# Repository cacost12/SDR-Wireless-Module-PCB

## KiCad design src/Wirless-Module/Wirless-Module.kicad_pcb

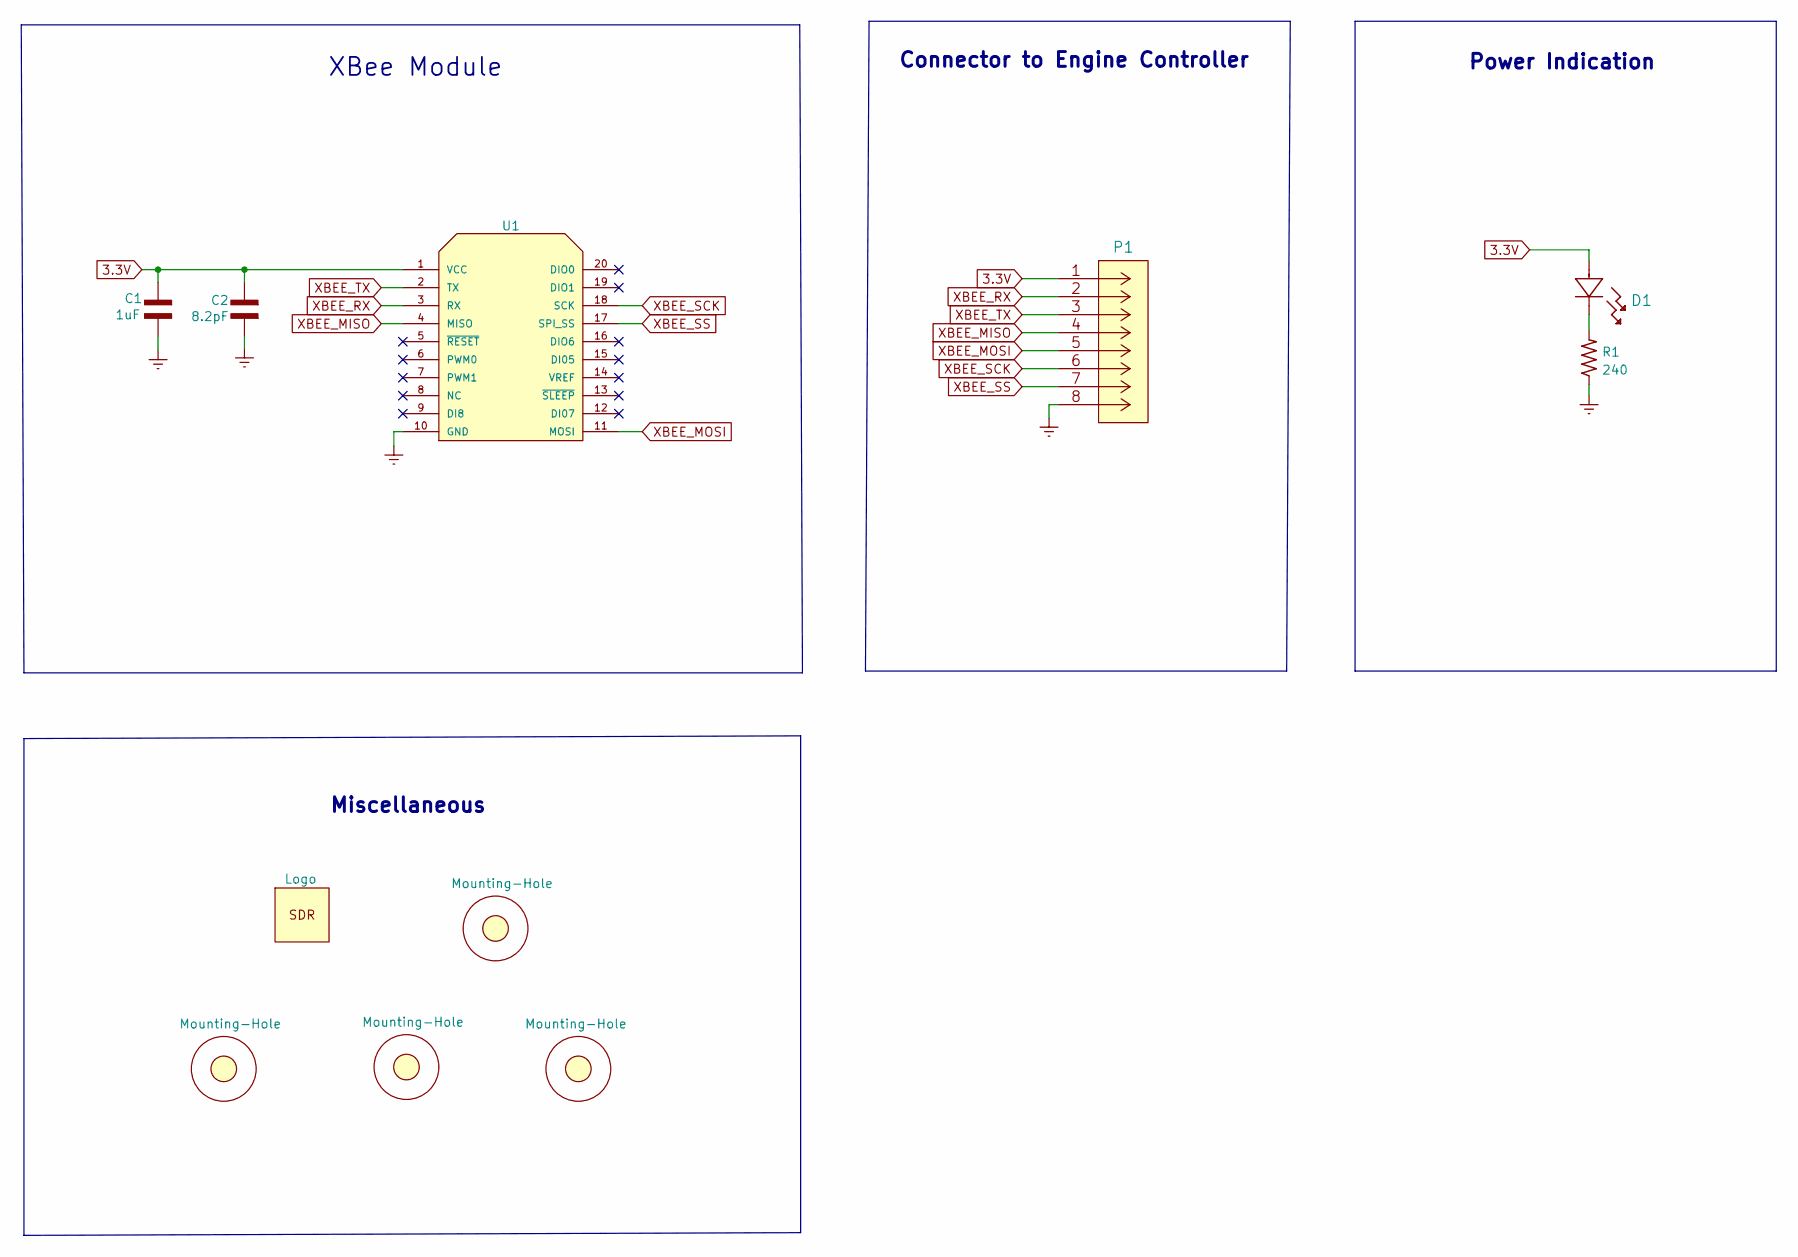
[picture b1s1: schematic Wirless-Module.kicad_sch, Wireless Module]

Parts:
C1: 1uF; CAP_0603
C2: 8.2pF; CAP_0603
D1: SML-LX1206GC-TR
H1, H2, H3, H4: Mounting-Hole; MountingHole_4.3mm_M4_DIN965
LOGO1: Logo
P1: 5015680807
R1: 240; RES_0603
U1: XB24CDMPIT-001; XBee

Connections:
3.3V: C1.1, C2.1, D1.2, P1.1, U1.1 (VCC)
Earth: C1.2, C2.2, P1.8, R1.1, U1.10 (GND)
unnamed: D1.1, R1.2
XBEE_MISO: P1.4, U1.4 (MISO)
XBEE_MOSI: P1.5, U1.11 (MOSI)
XBEE_RX: P1.2, U1.3 (RX)
XBEE_SCK: P1.6, U1.18 (SCK)
XBEE_SS: P1.7, U1.17 (SPI_SS)
XBEE_TX: P1.3, U1.2 (TX)

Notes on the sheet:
XBee Module
Connector to Engine Controller
Miscellaneous
Power Indication

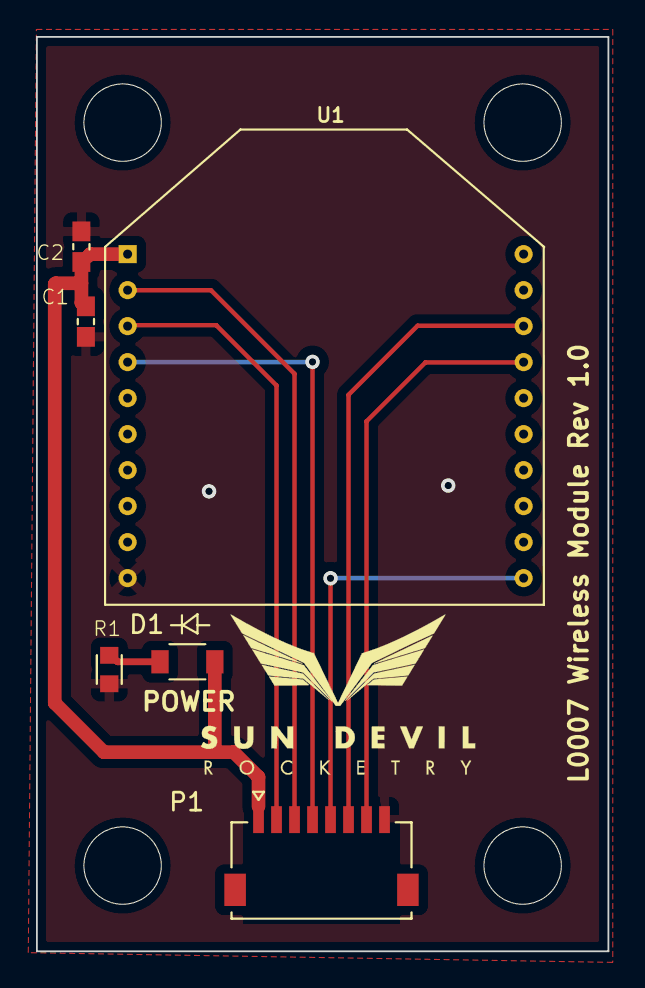
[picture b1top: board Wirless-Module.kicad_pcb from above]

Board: 2 copper layers, 31.8 x 50.8 mm, 11 parts (0 on the bottom side), 9 nets.

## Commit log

2023-05-19 copied over files from old repo

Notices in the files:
parts and their libraries:
Copyright 2021 Accelerated Designs. All rights reserved.
